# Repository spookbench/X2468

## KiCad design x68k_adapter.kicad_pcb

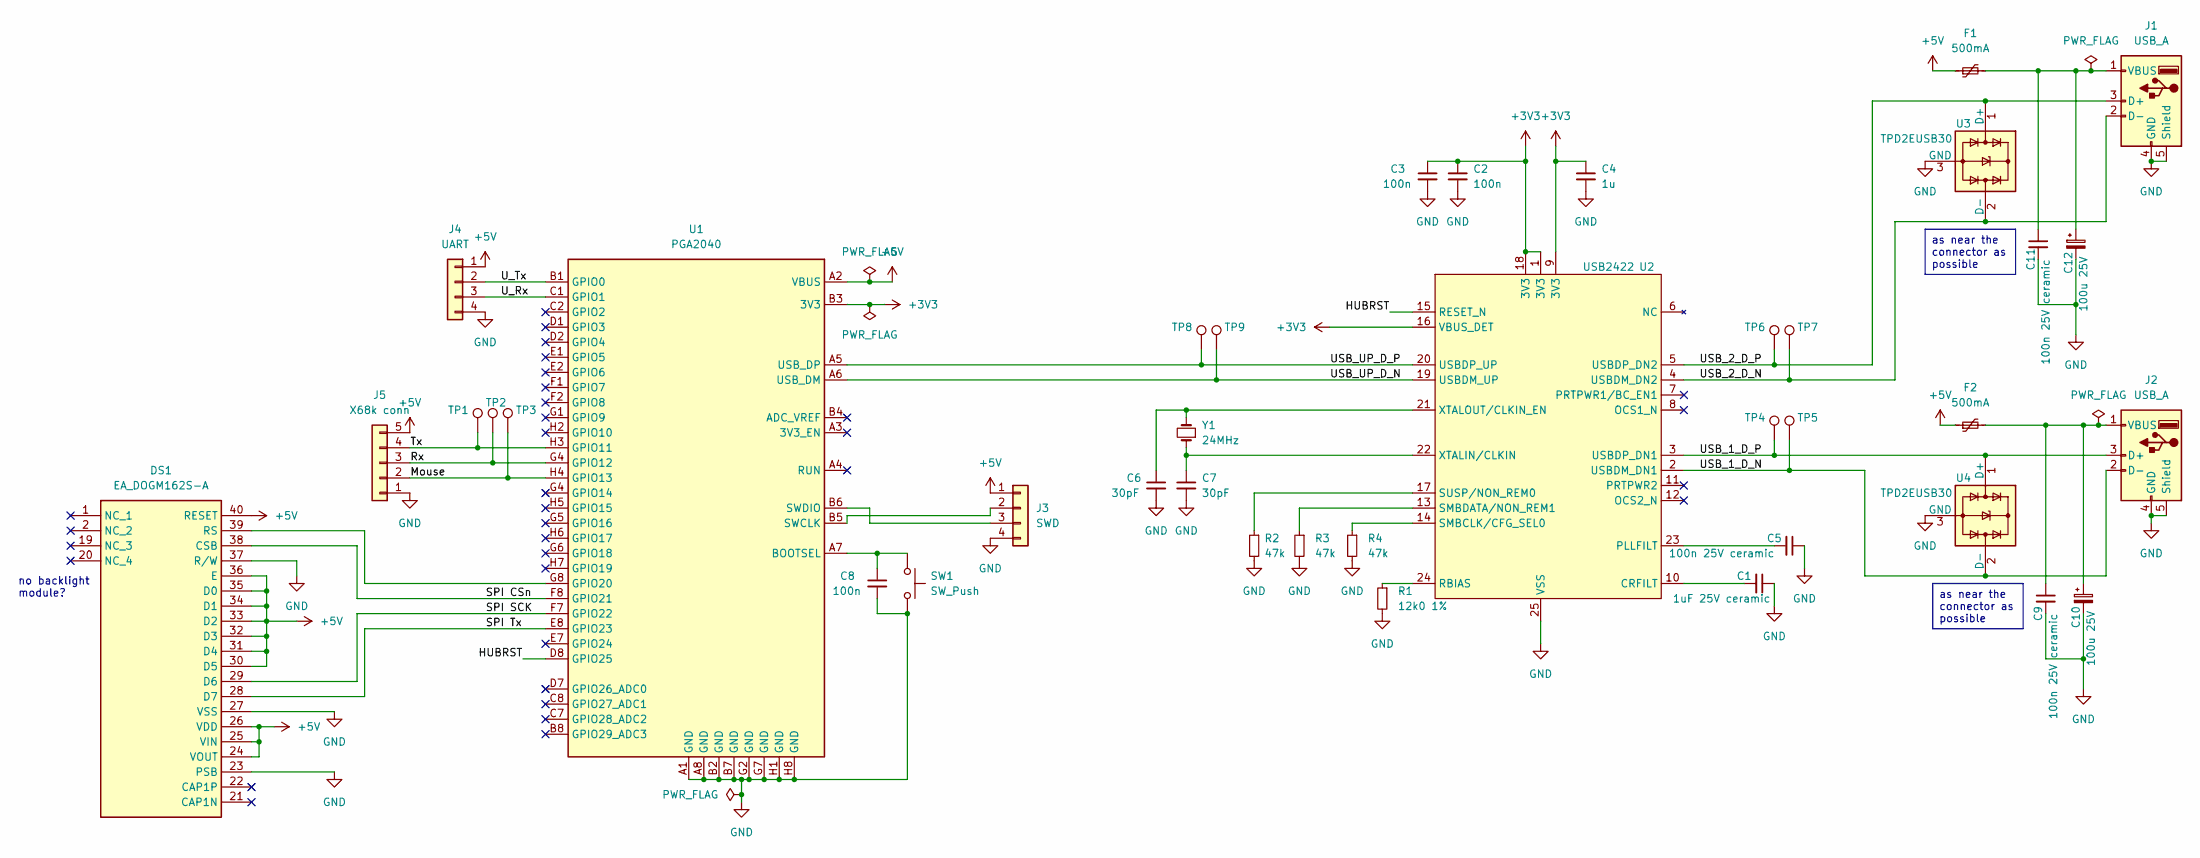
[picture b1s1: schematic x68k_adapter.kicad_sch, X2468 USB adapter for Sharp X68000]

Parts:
C1: 1uF 25V ceramic; C_1206_3216Metric_Pad1.33x1.80mm_HandSolder
C2, C3, C8: 100n; C_1206_3216Metric_Pad1.33x1.80mm_HandSolder
C4: 1u; C_1206_3216Metric_Pad1.33x1.80mm_HandSolder
C5, C9, C11: 100n 25V ceramic; C_1206_3216Metric_Pad1.33x1.80mm_HandSolder
C6, C7: 30pF; C_1206_3216Metric_Pad1.33x1.80mm_HandSolder
C10, C12: 100u 25V; C_1206_3216Metric_Pad1.33x1.80mm_HandSolder
DS1: EA_DOGM162S-A; EA_DOGM128-6; Manufacturer_Part_Number EA DOGM162S-A
F1, F2: 500mA; Fuse_1206_3216Metric_Pad1.42x1.75mm_HandSolder
J1, J2: USB_A; USB_A_Molex_67643_Horizontal
J3: SWD; PinHeader_1x04_P2.54mm_Vertical
J4: UART; PinHeader_1x04_P2.54mm_Vertical
J5: X68k conn; PinHeader_1x05_P2.54mm_Vertical
R1: 12k0 1%; R_0603_1608Metric_Pad0.98x0.95mm_HandSolder
R2, R3, R4: 47k; R_0603_1608Metric_Pad0.98x0.95mm_HandSolder
SW1: SW_Push; SW_PUSH_6mm
TP1, TP2, TP3, TP4, TP5, TP6, TP7, TP8, TP9: TestPoint; TestPoint_Pad_1.0x1.0mm
U1: PGA2040; PGA48
U2: USB2422; QFN-24-1EP_4x4mm_P0.5mm_EP2.6x2.6mm
U3, U4: TPD2EUSB30; Texas_DRT-3
Y1: 24MHz; Crystal_HC49-4H_Vertical

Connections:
+3V3: C2.1, C3.1, C4.1, U1.B3 (3V3), U2.1 (3V3), U2.9 (3V3), U2.16 (VBUS_DET), U2.18 (3V3)
+5V: DS1.24 (VOUT), DS1.25 (VIN), DS1.26 (VDD), DS1.30 (D5), DS1.31 (D4), DS1.32 (D3), DS1.33 (D2), DS1.34 (D1), DS1.35 (D0), DS1.36 (E), DS1.40 (RESET), F1.1, F2.1, J3.1, J4.1, J5.5, U1.A2 (VBUS)
/HUBRST: U1.D8 (GPIO25), U2.15 (RESET_N)
/Mouse: J5.2, TP3.1, U1.H4 (GPIO13)
/Rx: J5.3, TP2.1, U1.G4 (GPIO12)
/SPI CSn: DS1.38 (CSB), U1.F8 (GPIO21)
/SPI SCK: DS1.29 (D6), U1.F7 (GPIO22)
/SPI Tx: DS1.28 (D7), U1.E8 (GPIO23)
/Tx: J5.4, TP1.1, U1.H3 (GPIO11)
/USB_1_D_N: J2.2 (D-), TP5.1, U2.2 (USBDM_DN1), U4.2 (D-)
/USB_1_D_P: J2.3 (D+), TP4.1, U2.3 (USBDP_DN1), U4.1 (D+)
/USB_2_D_N: J1.2 (D-), TP7.1, U2.4 (USBDM_DN2), U3.2 (D-)
/USB_2_D_P: J1.3 (D+), TP6.1, U2.5 (USBDP_DN2), U3.1 (D+)
/USB_UP_D_N: TP9.1, U1.A6 (USB_DM), U2.19 (USBDM_UP)
/USB_UP_D_P: TP8.1, U1.A5 (USB_DP), U2.20 (USBDP_UP)
/U_Rx: J4.3, U1.C1 (GPIO1)
/U_Tx: J4.2, U1.B1 (GPIO0)
GND: C1.1, C2.2, C3.2, C4.2, C5.1, C6.2, C7.2, C8.2, C9.2, C10.2, C11.2, C12.2, DS1.23 (PSB), DS1.27 (VSS), DS1.37 (R/W), J1.4 (GND), J1.5 (Shield), J2.4 (GND), J2.5 (Shield), J3.4, J4.4, J5.1, R1.2, R2.2, R3.2, R4.2, SW1.2, U1.A1 (GND), U1.A8 (GND), U1.B2 (GND), U1.B7 (GND), U1.G2 (GND), U1.G7 (GND), U1.H1 (GND), U1.H8 (GND), U2.25 (VSS), U3.3 (GND), U4.3 (GND)
unnamed: DS1.39 (RS), U1.G8 (GPIO20)
unnamed: C11.1, C12.1, F1.2, J1.1 (VBUS)
unnamed: C9.1, C10.1, F2.2, J2.1 (VBUS)
unnamed: J3.2, U1.B5 (SWCLK)
unnamed: J3.3, U1.B6 (SWDIO)
unnamed: C8.1, SW1.1, U1.A7 (BOOTSEL)
unnamed: C1.2, U2.10 (CRFILT)
unnamed: C5.2, U2.23 (PLLFILT)
unnamed: R1.1, U2.24 (RBIAS)
unnamed: R4.1, U2.14 (SMBCLK/CFG_SEL0)
unnamed: R3.1, U2.13 (SMBDATA/NON_REM1)
unnamed: R2.1, U2.17 (SUSP/NON_REM0)
unnamed: C7.1, U2.22 (XTALIN/CLKIN), Y1.1
unnamed: C6.1, U2.21 (XTALOUT/CLKIN_EN), Y1.2

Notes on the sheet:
as near the connector as possible
no backlight module?

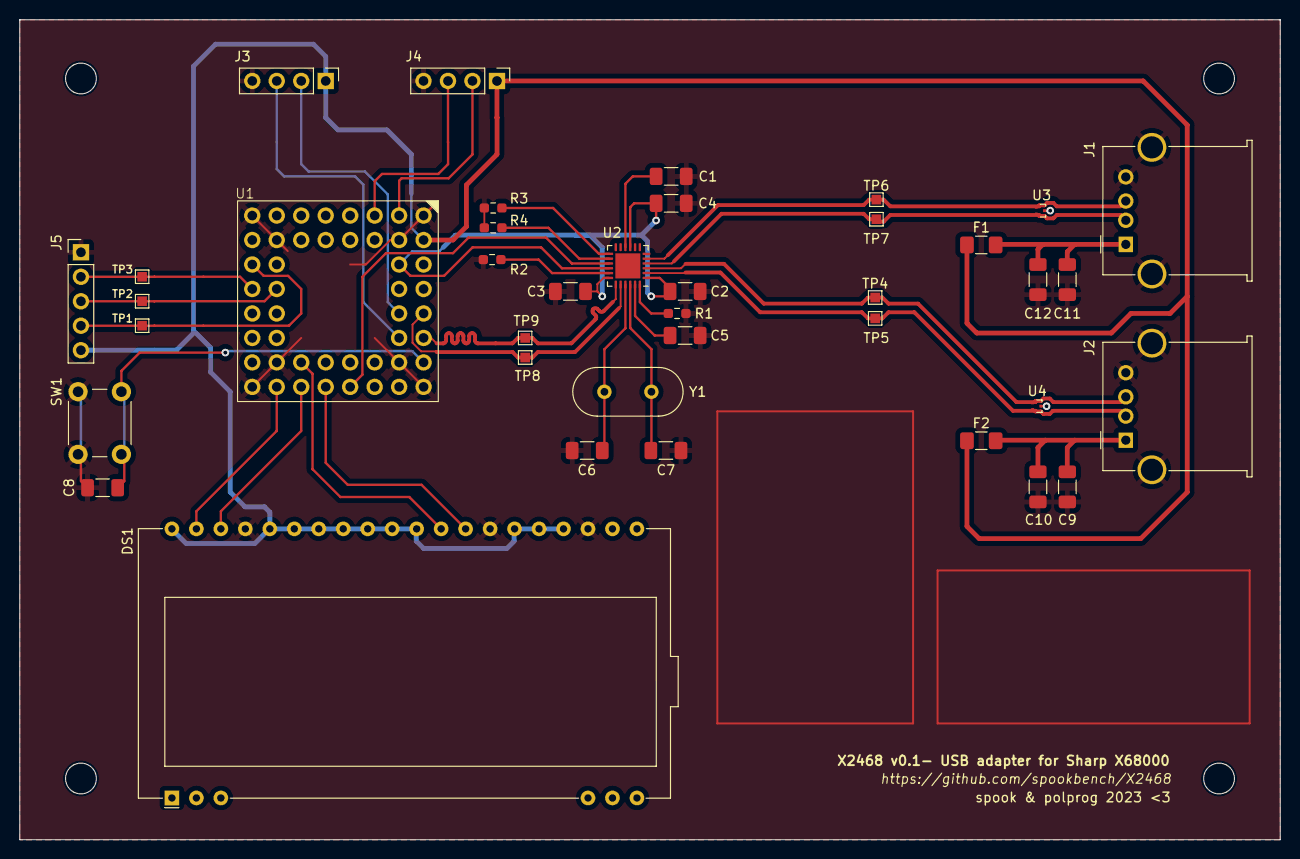
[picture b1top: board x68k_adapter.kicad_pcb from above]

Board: 4 copper layers, 130.8 x 85.1 mm, 39 parts (0 on the bottom side), 32 nets.

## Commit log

2023-07-27 ERC passes now
2023-08-05 Assign footprints
2023-08-05 route strap resistors
2023-08-06 add .gitignore
2023-08-06 recover autosave
2023-08-06 General placement of the components
2023-08-14 Add LCD and finish USB DPs
2023-08-19 Fix LCD footprint
2023-08-23 Final placement
